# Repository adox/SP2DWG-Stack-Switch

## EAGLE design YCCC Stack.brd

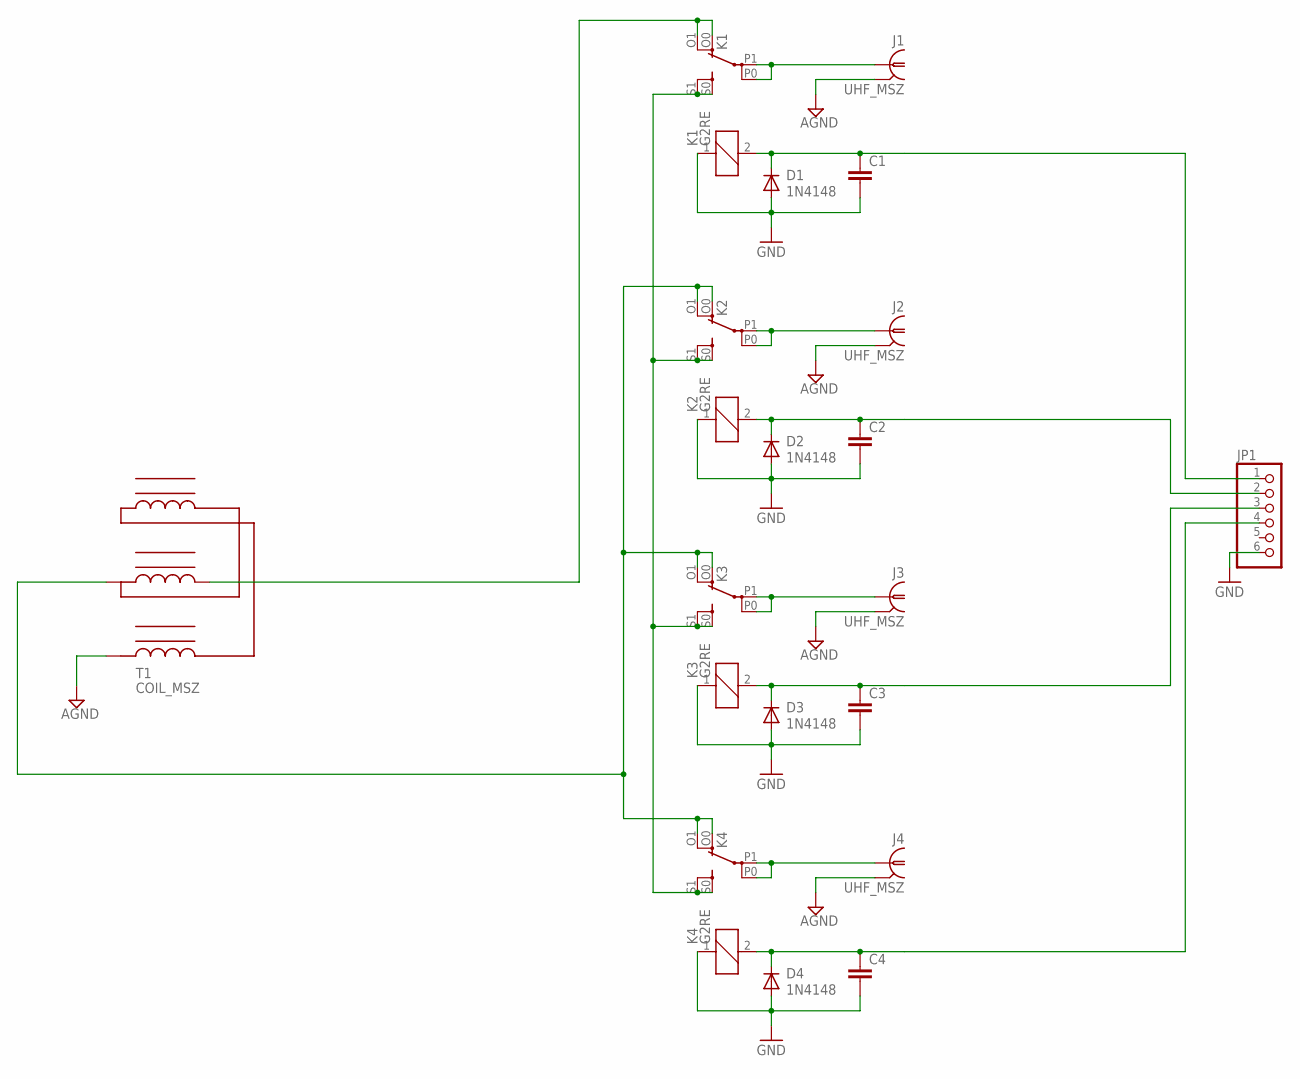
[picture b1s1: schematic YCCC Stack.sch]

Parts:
C1, C2, C3, C4: C-EU050-035X075; C050-035X075
D1, D2, D3, D4: 1N4148; DO35-7
J1, J2, J3, J4: UHF_MSZ; BNC_MSZ
JP1: PINHD-1X6; 1X06
K1, K2, K3, K4: G2RE
T1: COIL_MSZ

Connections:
AGND: J1.P$1 (GND), J2.P$1 (GND), J3.P$1 (GND), J4.P$1 (GND), T1.3 (GND)
GND: C1.2, C2.2, C3.2, C4.2, D1.A, D2.A, D3.A, D4.A, JP1.6, K1.1, K2.1, K3.1, K4.1
unnamed: C1.1, D1.C, JP1.1, K1.2
unnamed: J1.P$2 (1), K1.P0, K1.P1
unnamed: C2.1, D2.C, JP1.2, K2.2
unnamed: J2.P$2 (1), K2.P0, K2.P1
unnamed: C3.1, D3.C, JP1.3, K3.2
unnamed: J3.P$2 (1), K3.P0, K3.P1
unnamed: C4.1, D4.C, JP1.4, K4.2
unnamed: J4.P$2 (1), K4.P0, K4.P1
unnamed: K1.S0 (S), K1.S1 (S), K2.S0 (S), K2.S1 (S), K3.S0 (S), K3.S1 (S), K4.S0 (S), K4.S1 (S)
unnamed: K1.O0 (O), K1.O1 (O), T1.1 (50)
unnamed: K2.O0 (O), K2.O1 (O), K3.O0 (O), K3.O1 (O), K4.O0 (O), K4.O1 (O), T1.2 (22)

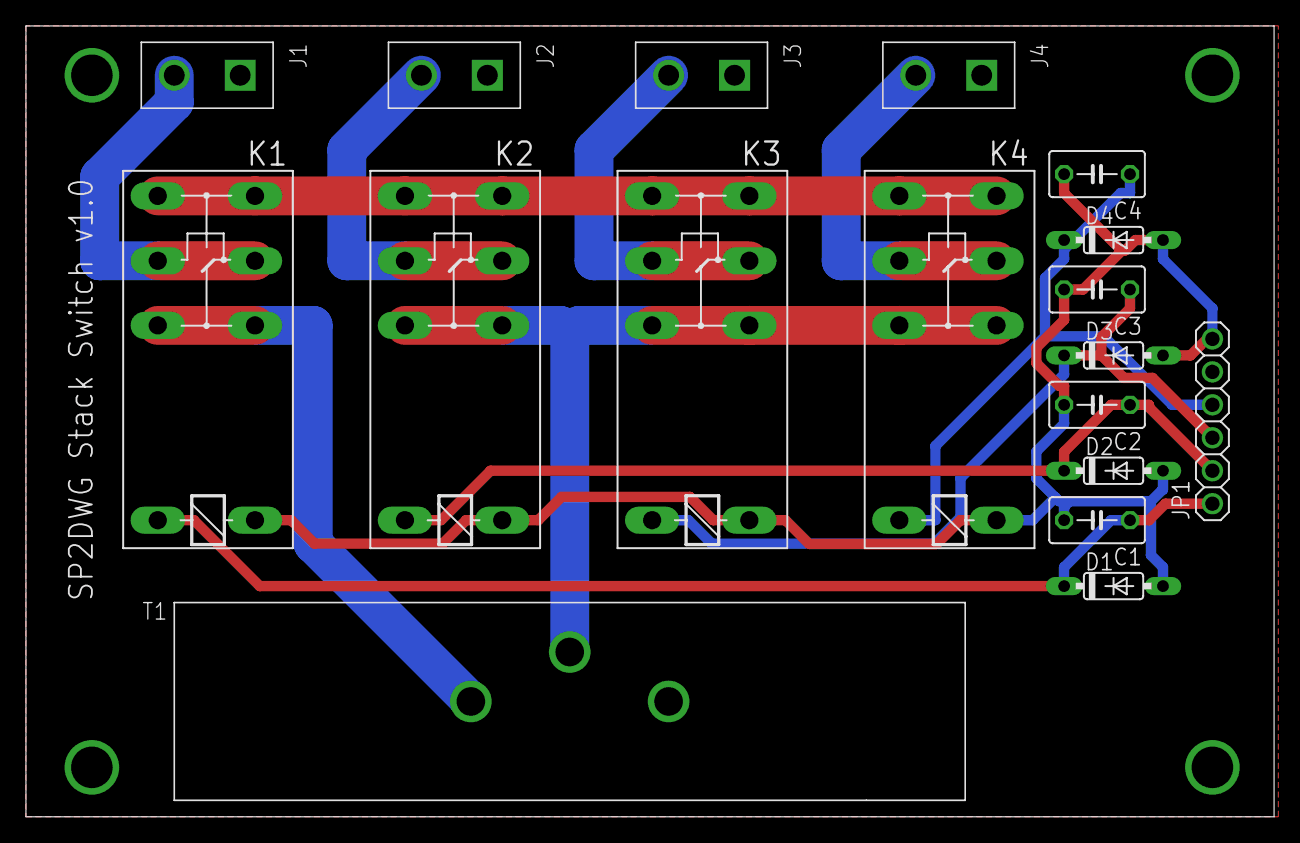
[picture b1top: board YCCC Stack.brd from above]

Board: 2 copper layers, 96.2 x 61.0 mm, 18 parts (0 on the bottom side), 13 nets.
